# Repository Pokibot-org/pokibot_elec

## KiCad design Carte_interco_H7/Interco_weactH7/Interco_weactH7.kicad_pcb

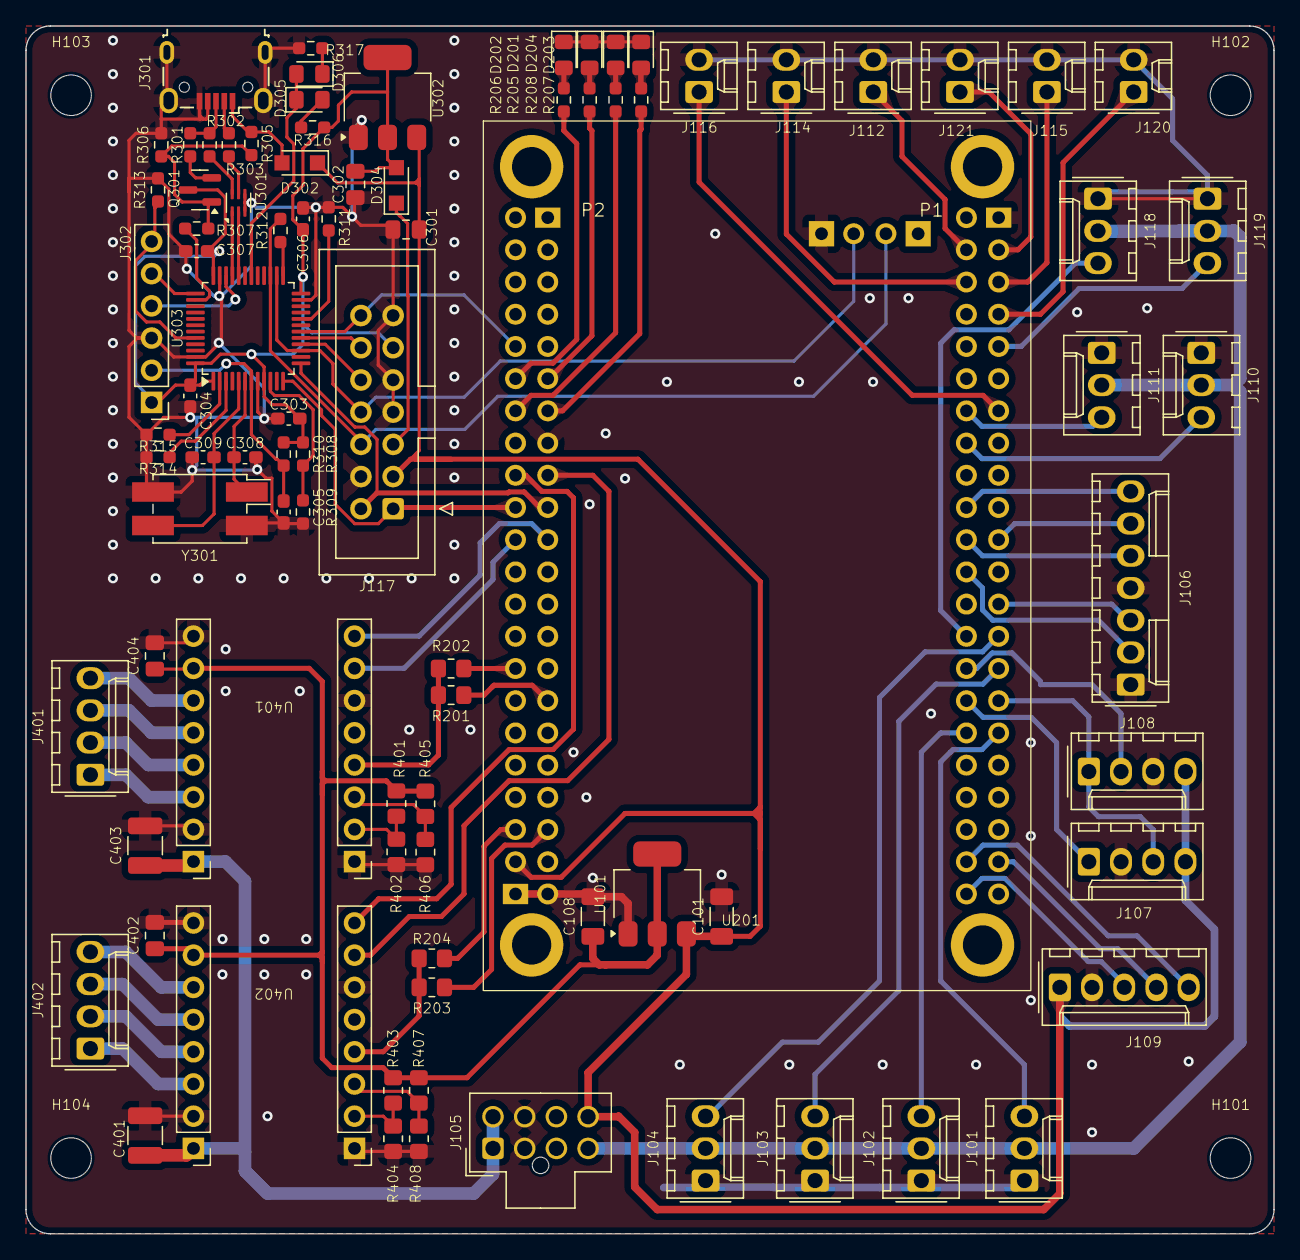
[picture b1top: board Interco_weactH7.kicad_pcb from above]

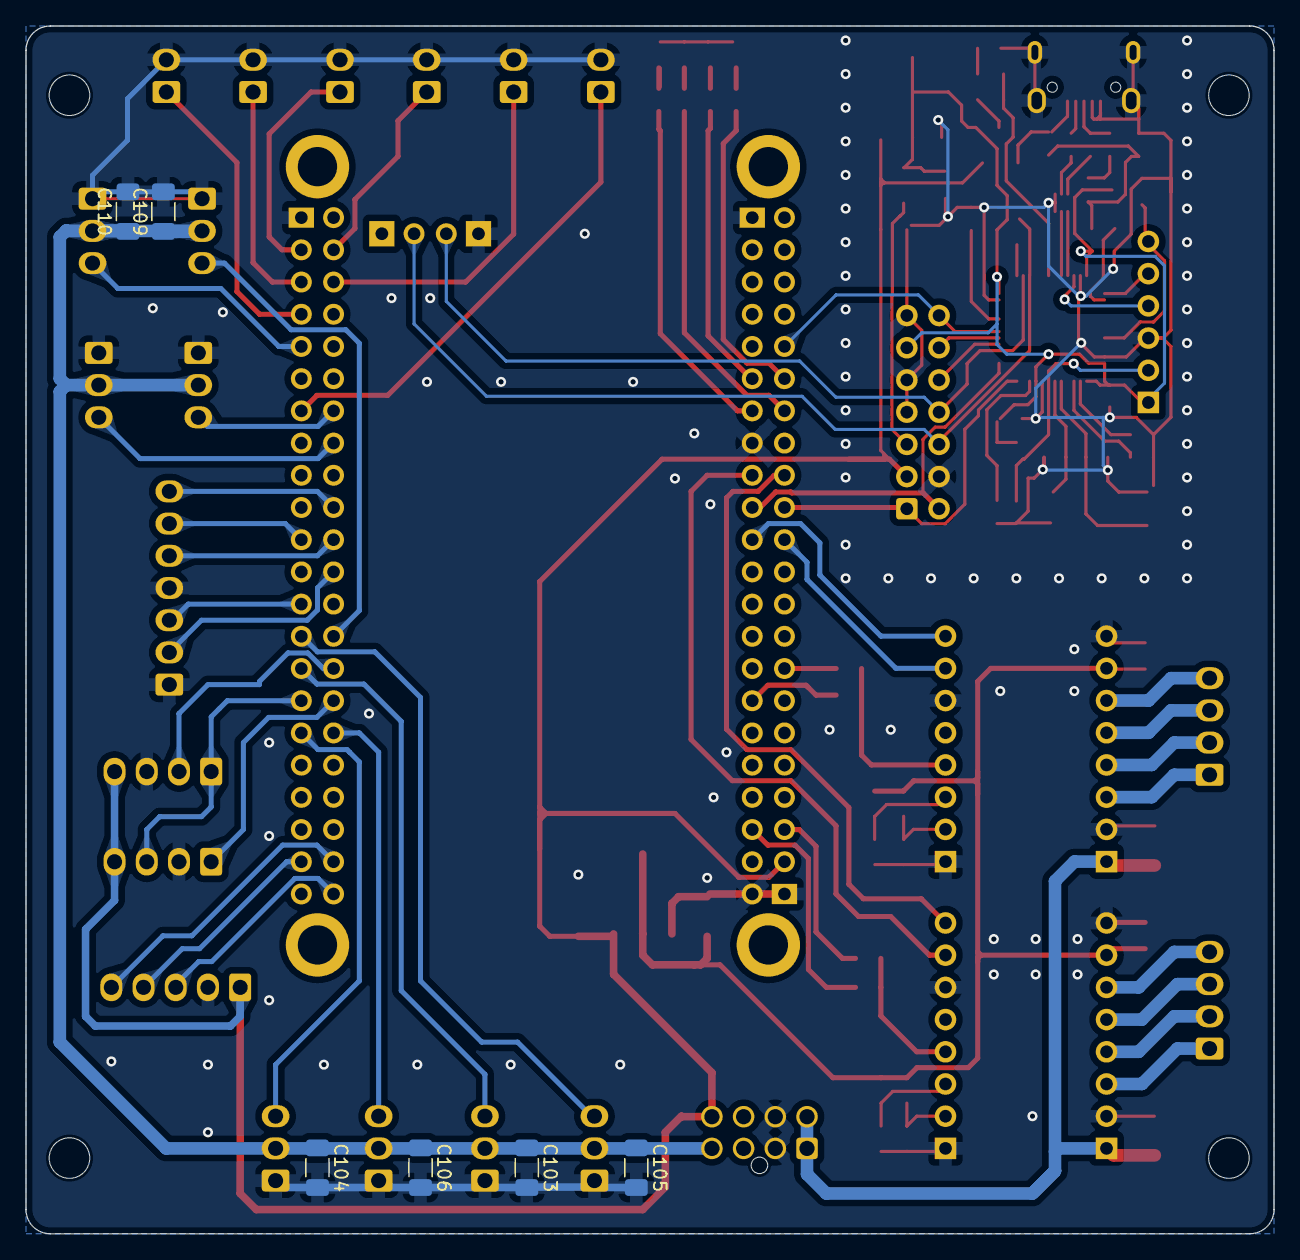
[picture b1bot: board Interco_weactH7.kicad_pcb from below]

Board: 2 copper layers, 98.4 x 95.3 mm, 98 parts (6 on the bottom side), 93 nets.

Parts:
C101, C103, C104, C105, C106, C108, C109, C110: 100n; C_1206_3216Metric_Pad1.33x1.80mm_HandSolder
C301, C302, C402, C404: 10uF; C_0805_2012Metric_Pad1.18x1.45mm_HandSolder
C303, C304, C306, C307: 100nF; C_0603_1608Metric_Pad1.08x0.95mm_HandSolder
C305: C; C_0603_1608Metric_Pad1.08x0.95mm_HandSolder
C308, C309: 20pF; C_0603_1608Metric_Pad1.08x0.95mm_HandSolder
C401, C403: 47uF; C_1210_3225Metric_Pad1.33x2.70mm_HandSolder
D201, D202, D203, D204, D305, D306: LED; LED_0805_2012Metric_Pad1.15x1.40mm_HandSolder
D302, D304: PMEG40T10ER; Nexperia_CFP3_SOD-123W
H101, H102, H103, H104: M1; MountingHole_3.2mm_M3
J101, J110, J118: servo orientation; Molex_KK-254_AE-6410-03A_1x03_P2.54mm_Vertical
J102, J111, J119: servo bras; Molex_KK-254_AE-6410-03A_1x03_P2.54mm_Vertical
J103, J104: servo dicristaline; Molex_KK-254_AE-6410-03A_1x03_P2.54mm_Vertical
J105: POW_access; Molex_Nano-Fit_105310-xx08_2x04_P2.50mm_Vertical
J106: KK-254_AE-6410-07A; Molex_KK-254_AE-6410-07A_1x07_P2.54mm_Vertical
J107, J108: LIDAR; Molex_KK-254_AE-6410-04A_1x04_P2.54mm_Vertical
J109: SNDBOARD; Molex_KK-254_AE-6410-05A_1x05_P2.54mm_Vertical
J112: Tirette; Molex_KK-254_AE-6410-02A_1x02_P2.54mm_Vertical
J114, J116: SWcote; Molex_KK-254_AE-6410-02A_1x02_P2.54mm_Vertical
J115, J121: reset; Molex_KK-254_AE-6410-02A_1x02_P2.54mm_Vertical
J117: Conn_02x07_Odd_Even; IDC-Header_2x07_P2.54mm_Vertical
J120: SWrobot; Molex_KK-254_AE-6410-02A_1x02_P2.54mm_Vertical
J301: 629105150521; USB_Micro-B_Wuerth_629105150521
J302: Conn_01x06_Pin; PinHeader_1x06_P2.54mm_Vertical
J401, J402: KK-254_AE-6410-04A; Molex_KK-254_AE-6410-04A_1x04_P2.54mm_Vertical
Q301: MMBTA44; SOT-23
R201, R202, R203, R204, R401, R402, R403, R404, R405, R406, R407, R408: R_US; R_0805_2012Metric_Pad1.20x1.40mm_HandSolder
R205, R206, R207, R208, R301, R316, R317: 1k; R_0603_1608Metric_Pad0.98x0.95mm_HandSolder
R302, R303: 10R; R_0603_1608Metric_Pad0.98x0.95mm_HandSolder
R305, R315: 10k; R_0603_1608Metric_Pad0.98x0.95mm_HandSolder
R306: 33k; R_0603_1608Metric_Pad0.98x0.95mm_HandSolder
R307, R312: 100R; R_0603_1608Metric_Pad0.98x0.95mm_HandSolder
R308, R309: 4k7; R_0603_1608Metric_Pad0.98x0.95mm_HandSolder
R310, R311, R313: R_US; R_0603_1608Metric_Pad0.98x0.95mm_HandSolder
R314: DNP; R_0603_1608Metric_Pad0.98x0.95mm_HandSolder
U101, U302: LD1117S33TR_SOT223; SOT-223-3_TabPin2
U201: WeAct 32H7xx
U301: ECMF02-2AMX6; ST_UQFN-6L_1.5x1.7mm_P0.5mm
U303: STM32F103CBT6; LQFP-48_7x7mm_P0.5mm
U401, U402: TMC2209
Y301: 8MHz; Crystal_SMD_EuroQuartz_MQ-4Pin_7.0x5.0mm_HandSoldering

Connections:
+3.3VA: C302.1, C303.1, C304.1, C306.1, C307.1, D304.2 (A), J117.11, J302.1, Q301.3 (C), R308.1, R310.1, R316.1, U302.2 (VO), U303.1 (VBAT), U303.9 (VDDA), U303.24 (VDD), U303.36 (VDD), U303.48 (VDD)
+3V3: C108.1, C402.1, C404.1, R401.2, R403.2, R405.2, R407.2, U101.2 (VO), U401.10 (VDD), U402.10 (VDD)
+5V_LOGIC: C101.1, C301.1, D302.1 (K), J105.8, J107.4, J108.4, J109.1, J117.3, U101.3 (VI), U201.P2_42 (5V), U302.3 (VI)
+5V_PWR: C103.1, C104.1, C105.1, C106.1, C109.1, C110.1, J101.2, J102.2, J103.2, J104.2, J105.4, J110.2, J111.2, J118.2, J119.2
+BATT: C401.1, C403.1, J105.1, J105.5, U401.16 (VM), U402.16 (VM)
/LIDAR_RX: J107.1, U201.P1_32 (PC6)
/LIDAR_TX: J107.3, J108.1, U201.P1_31 (PC7)
/MOTOR_MISO: J106.6, U201.P1_21 (PC11)
/MOTOR_MOSI: J106.7, U201.P1_20 (PC12)
/MOTOR_RX(IN): J106.2, U201.P1_24 (PA12)
/MOTOR_SCK: J106.5, U201.P1_22 (PC10)
/MOTOR_TX(OUT): J106.3, U201.P1_25 (PA11)
/PWM_SERVO1: J101.3, U201.P1_33 (PD15)
/PWM_SERVO2: J102.3, U201.P1_34 (PD14)
/PWM_SERVO3: J103.3, U201.P1_29 (PC9)
/PWM_SERVO4: J104.3, U201.P1_27 (PA9)
/PWM_SERVO5: J118.3, U201.P1_28 (PA8)
/PWM_SERVO6: J119.3, U201.P1_9 (PB5)
/SB_RST: J109.3, U201.P1_44 (PB12)
/SB_RX: J109.5, U201.P1_42 (PB14)
/SB_TX: J109.4, U201.P1_41 (PB15)
/TMC/A01: J401.2, U401.13 (A1)
/TMC/A02: J401.1, U401.14 (A2)
/TMC/A11: J402.2, U402.13 (A1)
/TMC/A12: J402.1, U402.14 (A2)
/TMC/B01: J401.3, U401.12 (B1)
/TMC/B02: J401.4, U401.11 (B2)
/TMC/B11: J402.3, U402.12 (B1)
/TMC/B12: J402.4, U402.11 (B2)
/TMC/UART1: R201.2, R202.2, U401.4 (PDN)
/TMC/UART2: R203.2, R204.2, U402.4 (PDN)
/WEACT/DBG1: R205.1, U201.P2_11 (PC0)
/WEACT/DBG2: R206.1, U201.P2_12 (PC1)
/WEACT/DBG3: R207.1, U201.P2_13 (PC2)
/WEACT/DBG4: R208.1, U201.P2_14 (PC3)
/WEACT/PA1: U201.P2_18 (PA1), U402.8 (DIR)
/WEACT/PA4: U201.P2_21 (PA4), U401.8 (DIR)
/WEACT/PB7: J120.1, U201.P1_7 (PB7)
/WEACT/PB8: J114.1, U201.P1_6 (PB8)
/WEACT/PB9: J115.1, U201.P1_5 (PB9)
/WEACT/PD3: J110.3, U201.P1_16 (PD3)
/WEACT/PD5: J111.3, U201.P1_14 (PD5)
/WEACT/PD6: J116.1, U201.P1_13 (PD6)
/WEACT/PE0: J112.1, U201.P1_4 (PE0)
/WEACT/PE1: J121.1, U201.P1_3 (PE1)
/WEACT/TIM2_CH1: U201.P2_22 (PA5), U401.7 (STEP)
/WEACT/TIM3_CH3: J108.2, U201.P1_30 (PC8)
/WEACT/TIM5_CH1: U201.P2_17 (PA0), U402.7 (STEP)
/WEACT/UART7_RX: R202.1, U201.P2_30 (PE7)
/WEACT/UART7_TX: R201.1, U201.P2_31 (PE8)
/WEACT/USART2_RX: J117.1, U201.P2_20 (PA3), U303.12 (PA2)
/WEACT/USART2_TX: J117.2, U201.P2_19 (PA2), U303.13 (PA3)
/WEACT/USART3_RX: R204.1, U201.P2_40 (PB11)
/WEACT/USART3_TX: R203.1, U201.P2_39 (PB10)
/stlink/3V3_TARGET: D304.1 (K), J117.5
/stlink/BOOT0: J302.6, R313.1, U303.44 (BOOT0)
/stlink/LED: D305.1 (K), D306.2 (A), U303.30 (PA9)
/stlink/OSC_IN: C309.1, U303.5 (PD0), Y301.3
/stlink/OSC_OUT: C308.1, U303.6 (PD1), Y301.1
/stlink/SRST: C305.2, J302.2, R310.2, U303.7 (NRST)
/stlink/SWCLK: J302.5, U303.37 (PA14)
/stlink/SWDIO: J302.4, U303.34 (PA13)
/stlink/T_JTCK: J117.8, U201.D3 (SWDCK), U303.15 (PA5), U303.26 (PB13)
/stlink/T_JTDI: J117.12, U303.17 (PA7)
/stlink/T_JTDO: J117.10, U303.16 (PA6)
/stlink/T_JTMS: J117.6, R312.2, U201.D2 (SWDIO), U303.27 (PB14)
/stlink/T_NRST: J117.14, U201.P2_10 (NRST), U303.18 (PB0)
/stlink/USB_RENUM: R307.1, U303.38 (PA15)
GND: C101.2, C103.2, C104.2, C105.2, C106.2, C108.2, C109.2, C110.2, C301.2, C302.2, C303.2, C304.2, C305.1, C306.2, C307.2, C308.2, C309.2, C401.2, C402.2, C403.2, C404.2, D201.1 (K), D202.1 (K), D203.1 (K), D204.1 (K), J101.1, J102.1, J103.1, J104.1, J105.2, J105.6, J106.1, J106.4, J107.2, J108.3, J109.2, J110.1, J111.1, J112.2, J114.2, J115.2, J116.2, J117.4, J117.7, J117.9, J117.13, J118.1, J119.1, J120.2, J121.2, J301.4 (ID), J301.5 (GND), J301.6 (Shield), J302.3, R306.2, R309.2, R311.2, R313.2, R314.2, R315.2, R317.2, R402.1, R404.1, R406.1, R408.1, U101.1 (GND), U201.D4 (GND), U201.P1_1 (GND), U201.P2_1 (GND), U201.P2_15 (GND), U201.P2_43 (GND), U201.P2_44 (GND), U301.3 (GND), U301.4 (NC), U302.1 (GND), U303.8 (VSSA), U303.23 (VSS), U303.35 (VSS), U303.47 (VSS), U401.1 (EN), U401.6 (CLK), U401.9 (GND), U401.15 (GND), U402.1 (EN), U402.6 (CLK), U402.9 (GND), U402.15 (GND), Y301.2, Y301.4
unnamed: D201.2 (A), R205.2
unnamed: D202.2 (A), R206.2
unnamed: D203.2 (A), R207.2
unnamed: D204.2 (A), R208.2
unnamed: D302.2 (A), J301.1 (VBUS), R305.1
unnamed: D305.2 (A), R316.2
unnamed: D306.1 (K), R317.1
unnamed: J301.3 (D+), R301.2, R302.1
unnamed: J301.2 (D-), R303.1
unnamed: Q301.1 (B), R305.2, R306.1, R307.2
unnamed: Q301.2 (E), R301.1
unnamed: U301.1 (D+_in), U303.33 (PA12)
unnamed: R302.2, U301.6 (D+_out)
unnamed: U301.2 (D-_in), U303.32 (PA11)
unnamed: R303.2, U301.5 (D-_out)
unnamed: R308.2, R309.1, U303.10 (PA0)
unnamed: R311.1, U303.20 (PB2)
unnamed: R312.1, U303.25 (PB12)
unnamed: R315.1, U303.2 (PC13)
unnamed: R314.1, U303.3 (PC14)
unnamed: R401.1, R402.2, U401.2 (MS1)
unnamed: R405.1, R406.2, U401.3 (MS2)
unnamed: R403.1, R404.2, U402.2 (MS1)
unnamed: R407.1, R408.2, U402.3 (MS2)

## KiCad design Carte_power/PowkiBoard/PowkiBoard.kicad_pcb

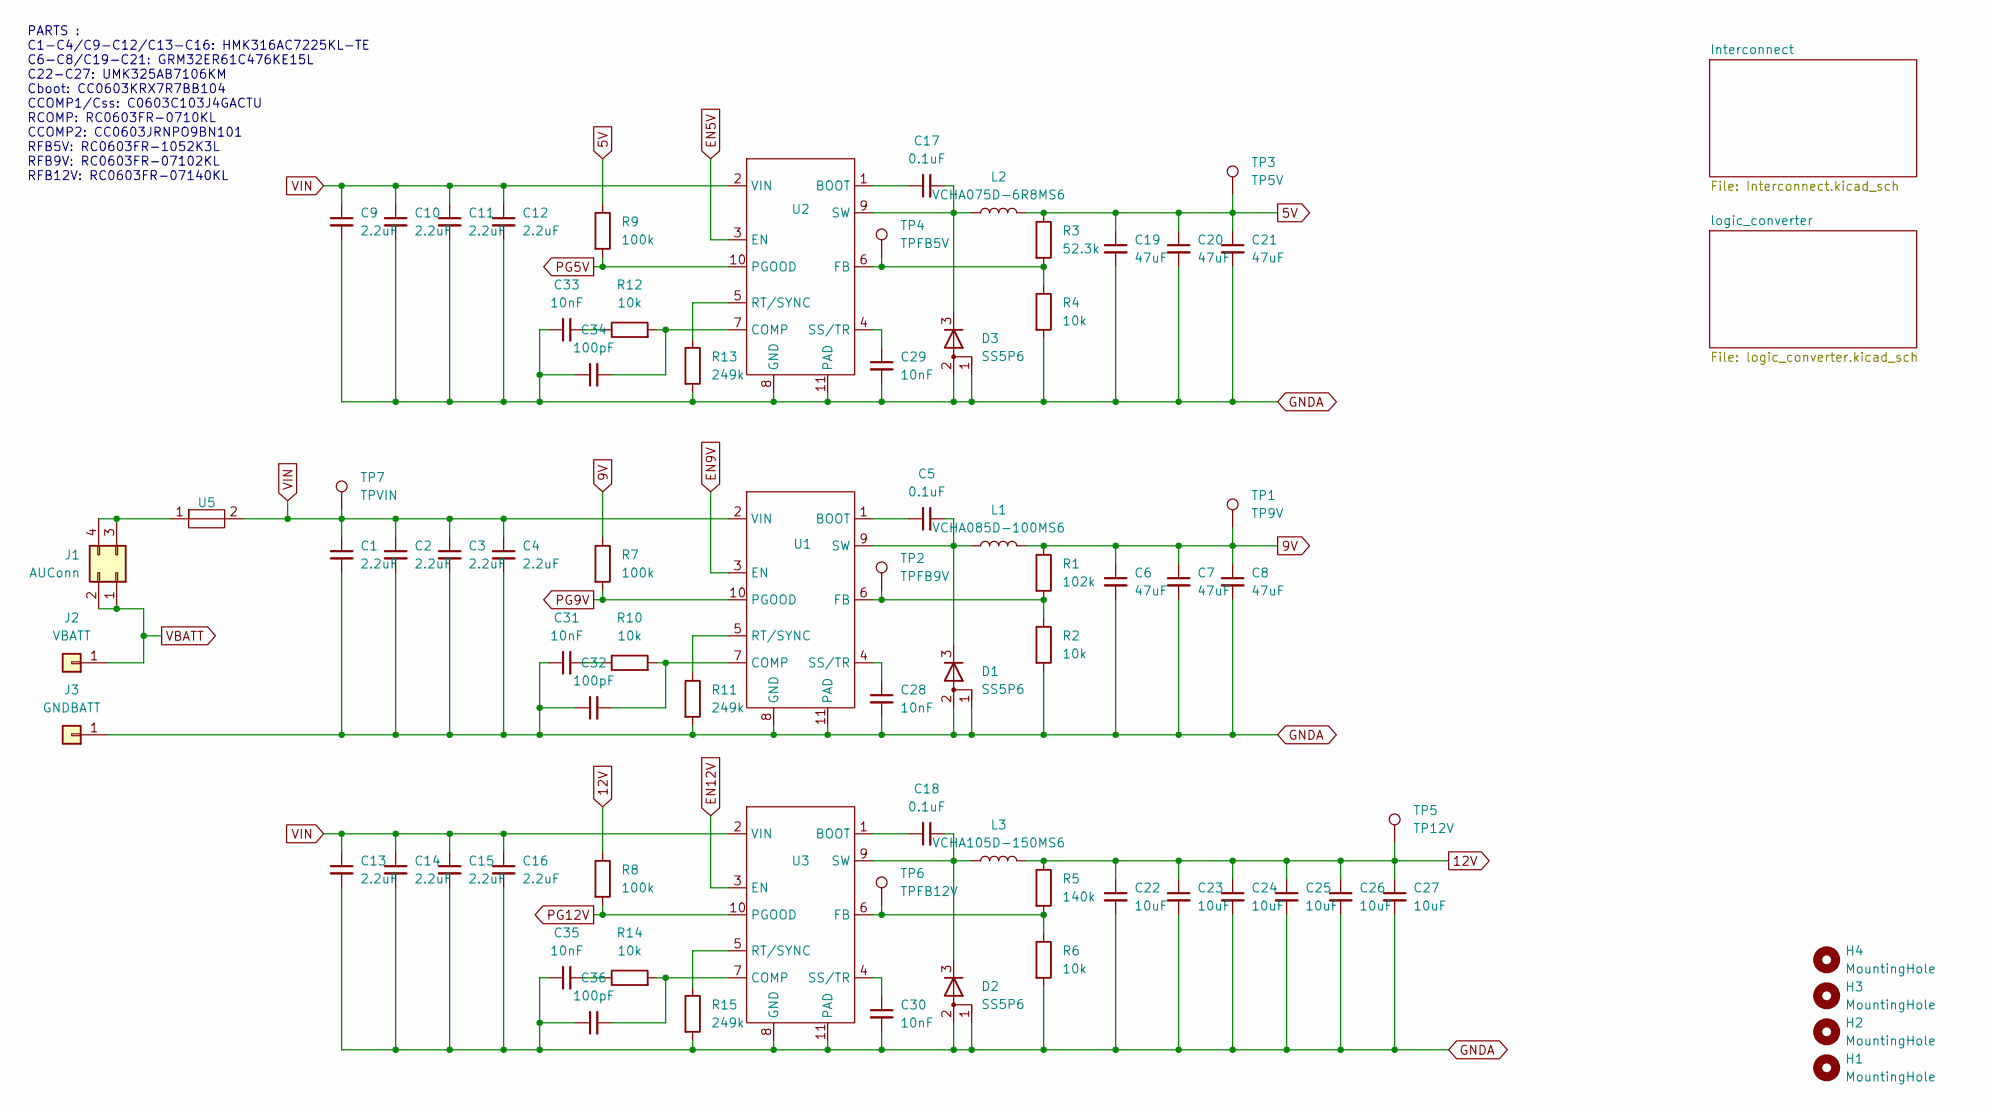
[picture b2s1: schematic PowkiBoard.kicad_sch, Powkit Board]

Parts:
C1, C2, C3, C4, C9, C10, C11, C12, C13, C14, C15, C16: 2.2uF; C_1206_3216Metric
C5, C17, C18: 0.1uF; C_0603_1608Metric
C6, C7, C8, C19, C20, C21: 47uF; C_1210_3225Metric
C22, C23, C24, C25, C26, C27: 10uF; C_1210_3225Metric
C28, C29, C30, C31, C33, C35: 10nF; C_0603_1608Metric
C32, C34, C36: 100pF; C_0603_1608Metric
D1, D2, D3: SS5P6; TO-277A
H1, H2, H3, H4: MountingHole; MountingHole_3.2mm_M3
J1: AUConn; Molex_Nano-Fit_105310-xx04_2x02_P2.50mm_Vertical
J2: VBATT; BATT_CONN
J3: GNDBATT; BATT_CONN
L1: VCHA085D-100MS6
L2: VCHA075D-6R8MS6
L3: VCHA105D-150MS6
R1: 102k; R_0603_1608Metric
R2, R4, R6, R10, R12, R14: 10k; R_0603_1608Metric
R3: 52.3k; R_0603_1608Metric
R5: 140k; R_0603_1608Metric
R7, R8, R9: 100k; R_0603_1608Metric
R11, R13, R15: 249k; R_0603_1608Metric
TP1: TP9V; TestPoint_Pad_D1.5mm
TP2: TPFB9V; TestPoint_Pad_D1.5mm
TP3: TP5V; TestPoint_Pad_D1.5mm
TP4: TPFB5V; TestPoint_Pad_D1.5mm
TP5: TP12V; TestPoint_Pad_D1.5mm
TP6: TPFB12V; TestPoint_Pad_D1.5mm
TP7: TPVIN; TestPoint_Pad_D1.5mm
U1, U2, U3: WDFN-10-1EP_3x3mm_P0.5mm_EP1.8x2.5mm
U5: 20x5_fuseholder

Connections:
5V: C19.1, C20.1, C21.1, L2.2, R3.1, R9.1, TP3.1; also elsewhere on the board
9V: C6.1, C7.1, C8.1, L1.2, R1.1, R7.1, TP1.1; also elsewhere on the board
12V: C22.1, C23.1, C24.1, C25.1, C26.1, C27.1, L3.2, R5.1, R8.1, TP5.1; also elsewhere on the board
EN12V: U1.3 (EN), U2.3 (EN), U3.3 (EN); also elsewhere on the board
GNDA: C1.2, C2.2, C3.2, C4.2, C6.2, C7.2, C8.2, C9.2, C10.2, C11.2, C12.2, C13.2, C14.2, C15.2, C16.2, C19.2, C20.2, C21.2, C22.2, C23.2, C24.2, C25.2, C26.2, C27.2, C28.2, C29.2, C30.2, C31.1, C32.1, C33.1, C34.1, C35.1, C36.1, D1.1 (A), D1.2 (A), D2.1 (A), D2.2 (A), D3.1 (A), D3.2 (A), J3.1, R2.2, R4.2, R6.2, R11.2, R13.2, R15.2, U1.8 (GND), U1.11 (PAD), U2.8 (GND), U2.11 (PAD), U3.8 (GND), U3.11 (PAD); also elsewhere on the board
unnamed: C31.2, R10.1
unnamed: C33.2, R12.1
unnamed: C35.2, R14.1
unnamed: C5.2, D1.3 (K), L1.1, U1.9 (SW)
unnamed: C18.2, D2.3 (K), L3.1, U3.9 (SW)
unnamed: C17.2, D3.3 (K), L2.1, U2.9 (SW)
unnamed: J1.3, J1.4, U5.1
unnamed: C5.1, U1.1 (BOOT)
unnamed: C32.2, R10.2, U1.7 (COMP)
unnamed: R1.2, R2.1, TP2.1, U1.6 (FB)
unnamed: R11.1, U1.5 (RT/SYNC)
unnamed: C28.1, U1.4 (SS/TR)
unnamed: C17.1, U2.1 (BOOT)
unnamed: C34.2, R12.2, U2.7 (COMP)
unnamed: R3.2, R4.1, TP4.1, U2.6 (FB)
unnamed: R13.1, U2.5 (RT/SYNC)
unnamed: C29.1, U2.4 (SS/TR)
unnamed: C18.1, U3.1 (BOOT)
unnamed: C36.2, R14.2, U3.7 (COMP)
unnamed: R5.2, R6.1, TP6.1, U3.6 (FB)
unnamed: R15.1, U3.5 (RT/SYNC)
unnamed: C30.1, U3.4 (SS/TR)
PG5V: R9.2, U2.10 (PGOOD); also elsewhere on the board
PG9V: R7.2, U1.10 (PGOOD); also elsewhere on the board
PG12V: R8.2, U3.10 (PGOOD); also elsewhere on the board
VBATT: J1.1, J1.2, J2.1; also elsewhere on the board
VIN: C1.1, C2.1, C3.1, C4.1, C9.1, C10.1, C11.1, C12.1, C13.1, C14.1, C15.1, C16.1, TP7.1, U1.2 (VIN), U2.2 (VIN), U3.2 (VIN), U5.2; also elsewhere on the board

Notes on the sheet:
PARTS : C1-C4/C9-C12/C13-C16: HMK316AC7225KL-TE C6-C8/C19-C21: GRM32ER61C476KE15L C22-C27: UMK325AB7106KM Cboot: CC0603KRX7R7BB104 CCOMP1/Css: C0603C103J4GACTU RCOMP: RC0603FR-0710KL CCOMP2: CC0603JRNPO9BN101 RFB5V: RC0603FR-1052K3L RFB9V: RC0603FR-07102KL RFB12V: RC0603FR-07140KL

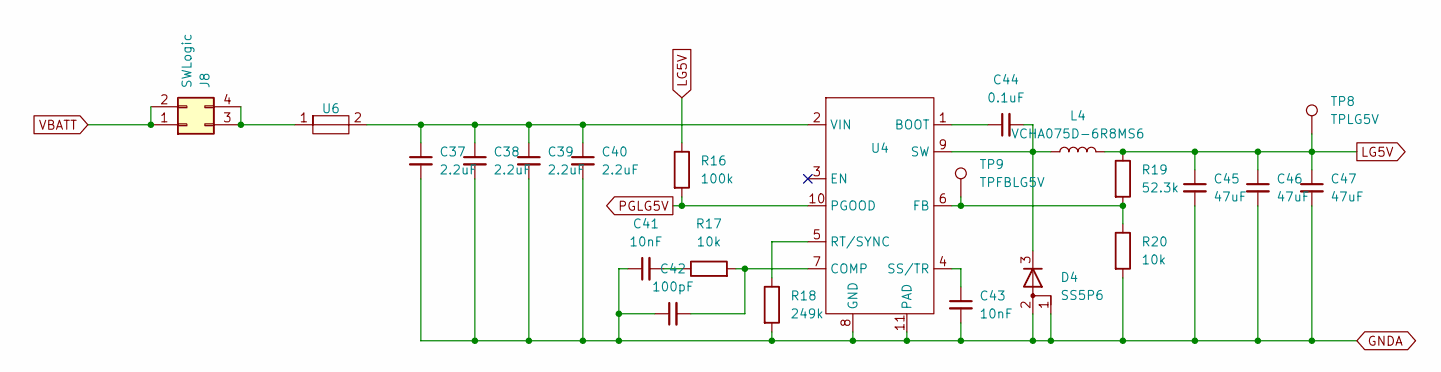
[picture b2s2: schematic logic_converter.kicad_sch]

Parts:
C37, C38, C39, C40: 2.2uF; C_1206_3216Metric
C41, C43: 10nF; C_0603_1608Metric
C42: 100pF; C_0603_1608Metric
C44: 0.1uF; C_0603_1608Metric
C45, C46, C47: 47uF; C_1210_3225Metric
D4: SS5P6; TO-277A
J8: SWLogic; Molex_Nano-Fit_105310-xx04_2x02_P2.50mm_Vertical
L4: VCHA075D-6R8MS6
R16: 100k; R_0603_1608Metric
R17, R20: 10k; R_0603_1608Metric
R18: 249k; R_0603_1608Metric
R19: 52.3k; R_0603_1608Metric
TP8: TPLG5V; TestPoint_Pad_D1.5mm
TP9: TPFBLG5V; TestPoint_Pad_D1.5mm
U4: WDFN-10-1EP_3x3mm_P0.5mm_EP1.8x2.5mm
U6: 20x5_fuseholder

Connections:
GNDA: C37.2, C38.2, C39.2, C40.2, C41.1, C42.1, C43.2, C45.2, C46.2, C47.2, D4.1 (A), D4.2 (A), R18.2, R20.2, U4.8 (GND), U4.11 (PAD); also elsewhere on the board
LG5V: C45.1, C46.1, C47.1, L4.2, R16.1, R19.1, TP8.1; also elsewhere on the board
unnamed: C41.2, R17.1
unnamed: C44.2, D4.3 (K), L4.1, U4.9 (SW)
unnamed: J8.3, J8.4, U6.1
unnamed: C44.1, U4.1 (BOOT)
unnamed: C42.2, R17.2, U4.7 (COMP)
unnamed: R19.2, R20.1, TP9.1, U4.6 (FB)
unnamed: R18.1, U4.5 (RT/SYNC)
unnamed: C43.1, U4.4 (SS/TR)
unnamed: C37.1, C38.1, C39.1, C40.1, U4.2 (VIN), U6.2
PGLG5V: R16.2, U4.10 (PGOOD); also elsewhere on the board
VBATT: J8.1, J8.2; also elsewhere on the board

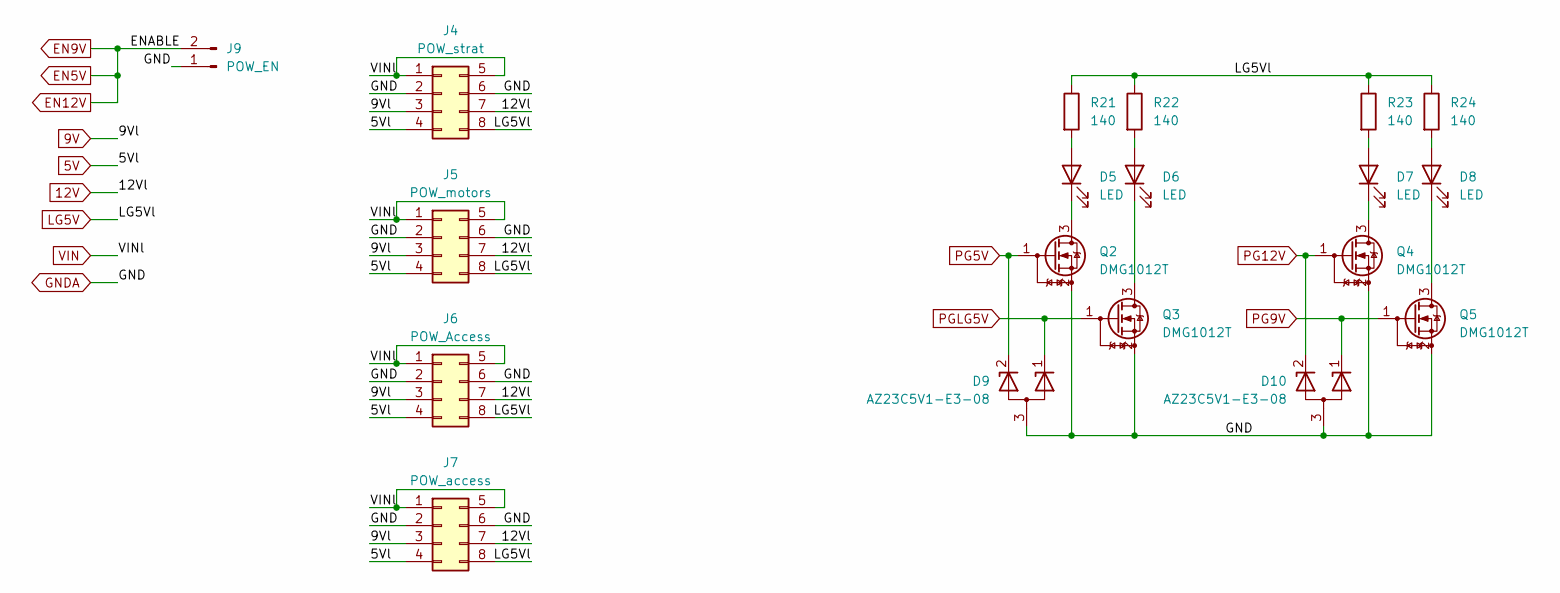
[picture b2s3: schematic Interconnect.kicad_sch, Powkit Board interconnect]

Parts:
D5, D6, D7, D8: LED; LED_D3.0mm
D9, D10: AZ23C5V1-E3-08; SOT-23
J4: POW_strat; Molex_Nano-Fit_105314-xx08_2x04_P2.50mm_Horizontal
J5: POW_motors; Molex_Nano-Fit_105314-xx08_2x04_P2.50mm_Horizontal
J6: POW_Access; Molex_Nano-Fit_105314-xx08_2x04_P2.50mm_Horizontal
J7: POW_access; Molex_Nano-Fit_105314-xx08_2x04_P2.50mm_Horizontal
J9: POW_EN; Molex_KK-254_AE-6410-02A_1x02_P2.54mm_Vertical
Q2, Q3, Q4, Q5: DMG1012T; SOT-523
R21, R22, R23, R24: 140; R_0603_1608Metric

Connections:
5V: J4.4, J5.4, J6.4, J7.4; also elsewhere on the board
9V: J4.3, J5.3, J6.3, J7.3; also elsewhere on the board
12V: J4.7, J5.7, J6.7, J7.7; also elsewhere on the board
EN12V: J9.2; also elsewhere on the board
GNDA: D9.3 (A), D10.3 (A), J4.2, J4.6, J5.2, J5.6, J6.2, J6.6, J7.2, J7.6, J9.1, Q2.2 (S), Q3.2 (S), Q4.2 (S), Q5.2 (S); also elsewhere on the board
LG5V: J4.8, J5.8, J6.8, J7.8, R21.1, R22.1, R23.1, R24.1; also elsewhere on the board
unnamed: D5.2 (A), R21.2
unnamed: D5.1 (K), Q2.3 (D)
unnamed: D6.2 (A), R22.2
unnamed: D6.1 (K), Q3.3 (D)
unnamed: D7.2 (A), R23.2
unnamed: D7.1 (K), Q4.3 (D)
unnamed: D8.2 (A), R24.2
unnamed: D8.1 (K), Q5.3 (D)
PG5V: D9.2 (K), Q2.1 (G); also elsewhere on the board
PG9V: D10.1 (K), Q5.1 (G); also elsewhere on the board
PG12V: D10.2 (K), Q4.1 (G); also elsewhere on the board
PGLG5V: D9.1 (K), Q3.1 (G); also elsewhere on the board
VIN: J4.1, J4.5, J5.1, J5.5, J6.1, J6.5, J7.1, J7.5; also elsewhere on the board

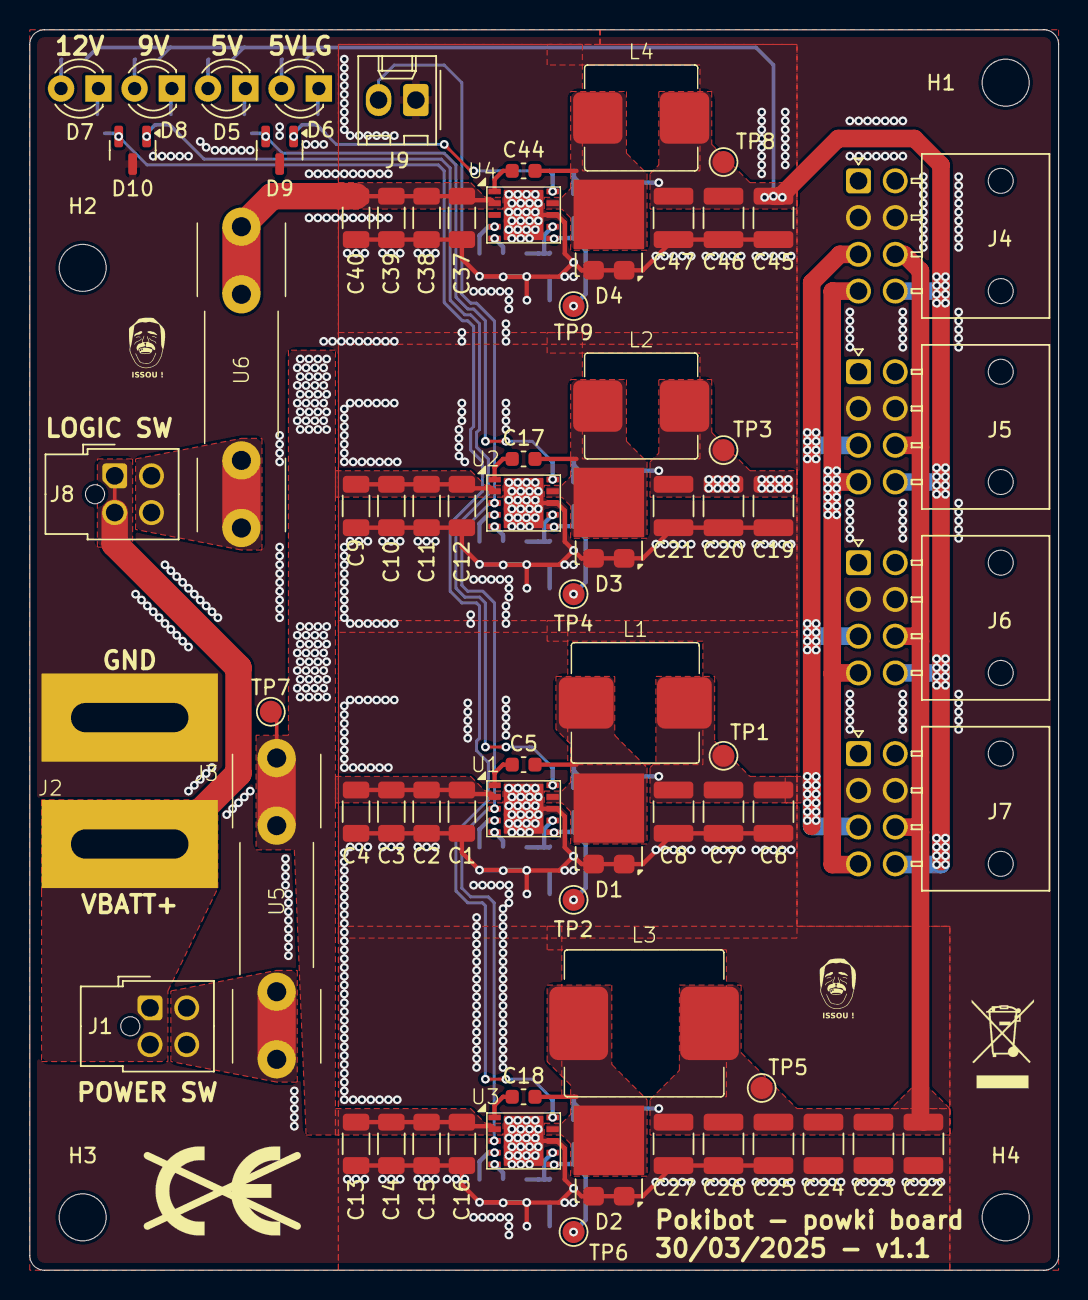
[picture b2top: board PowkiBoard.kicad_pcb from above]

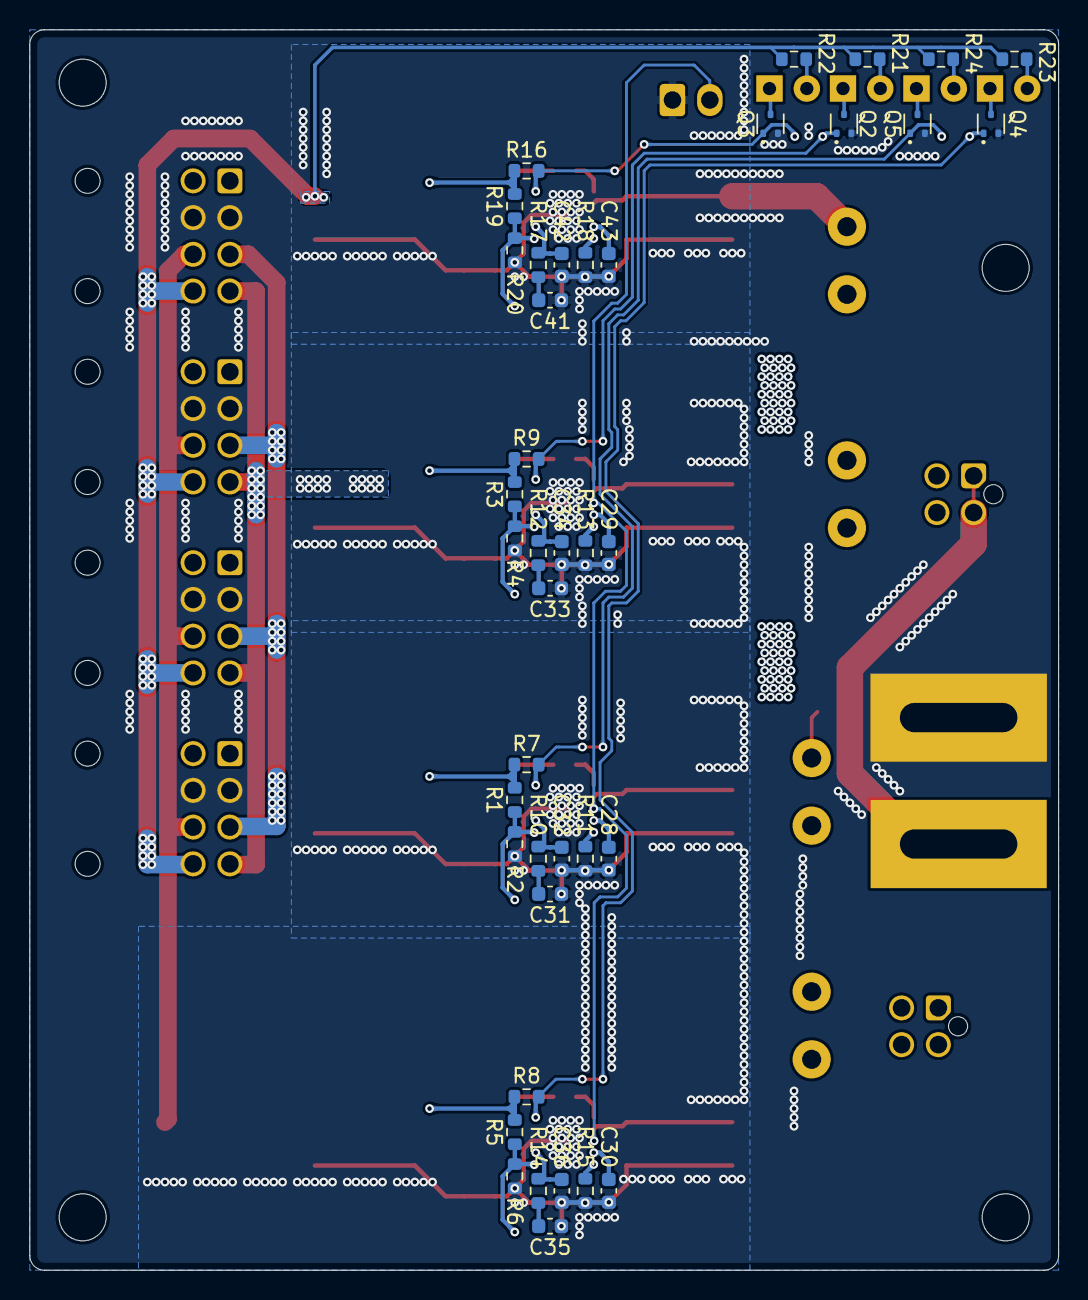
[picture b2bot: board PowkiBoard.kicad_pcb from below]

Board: 4 copper layers, 70.0 x 84.4 mm, 119 parts (40 on the bottom side), 51 nets.

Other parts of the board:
logo1: CE-Logo_8.5x6mm_SilkScreen
logo2: WEEE-Logo_4.2x6mm_SilkScreen

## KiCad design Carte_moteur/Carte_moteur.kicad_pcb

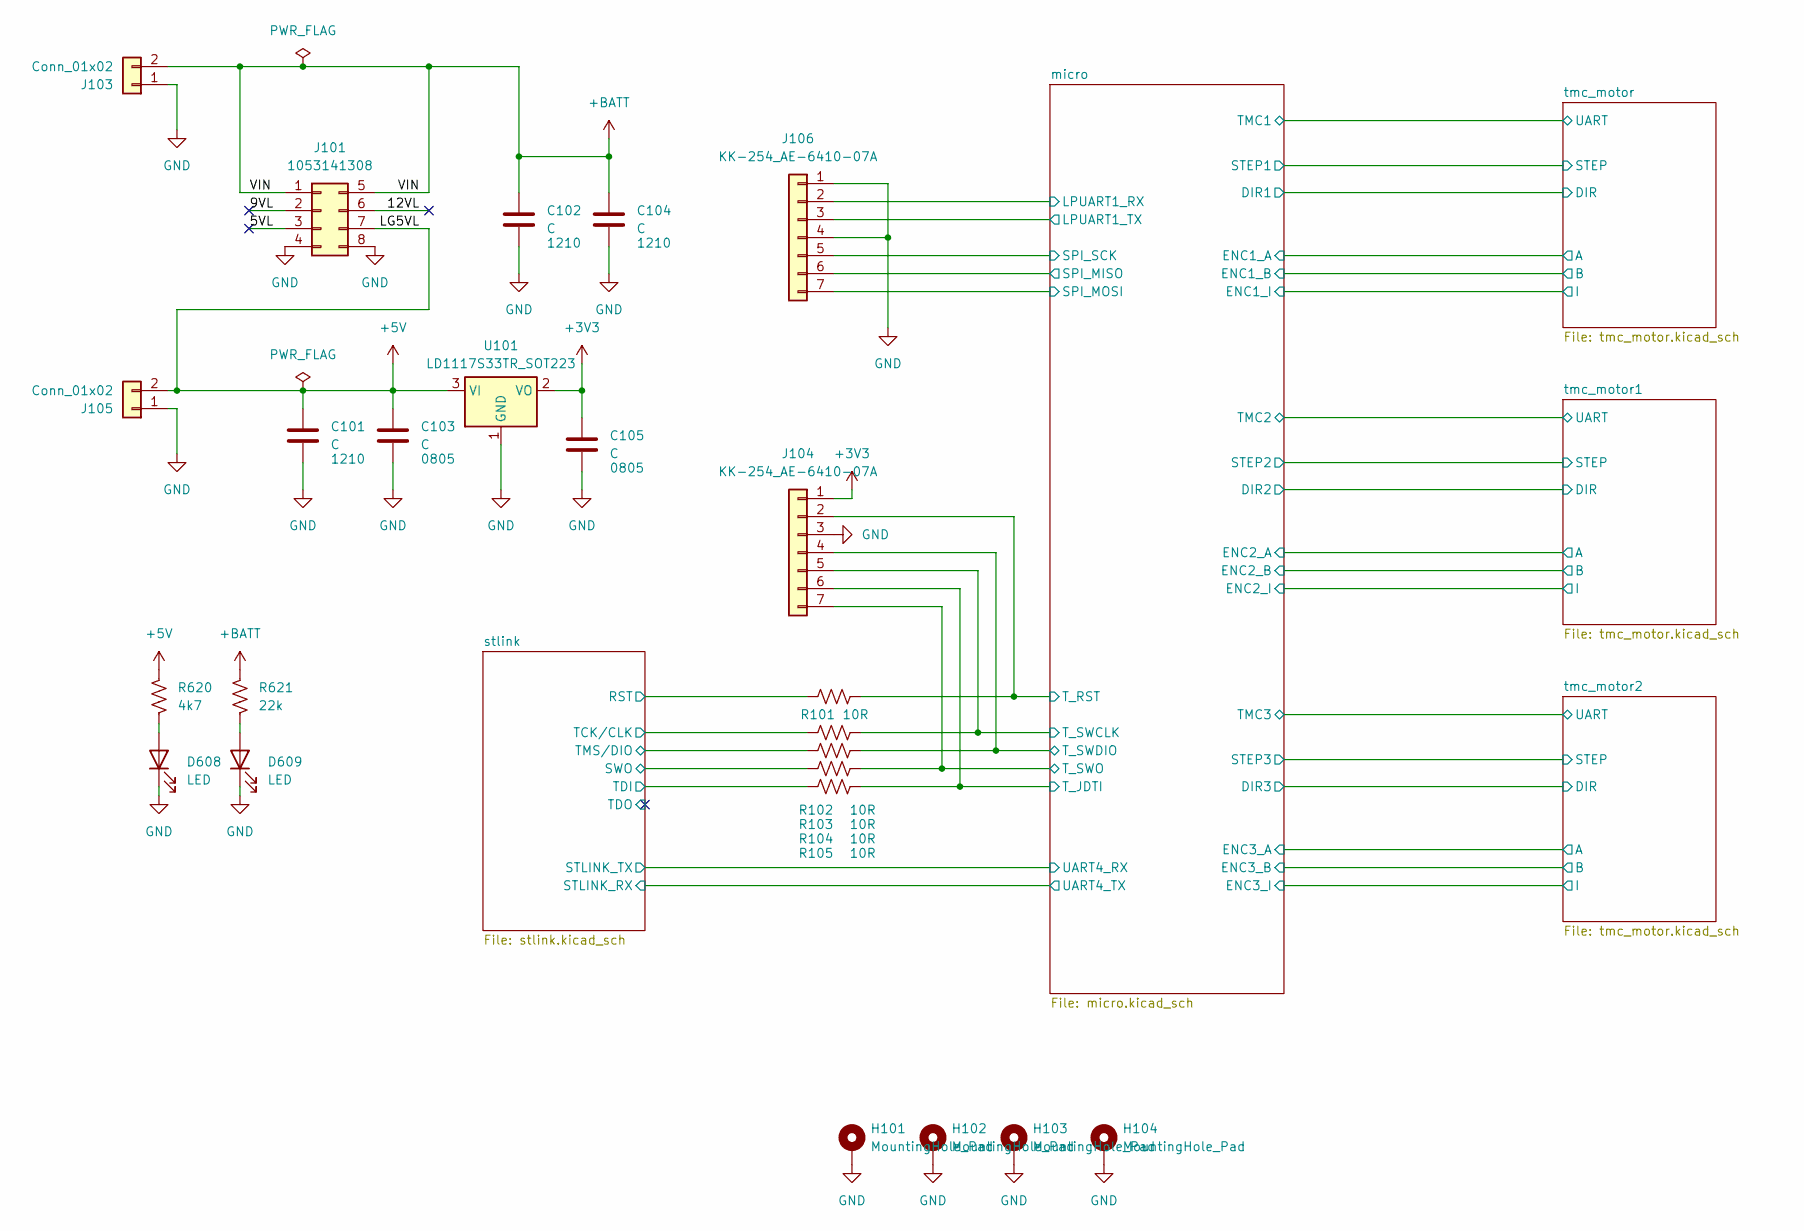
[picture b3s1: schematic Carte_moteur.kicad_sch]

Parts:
C101, C102, C104: C; C_1210_3225Metric_Pad1.33x2.70mm_HandSolder
C103, C105: C; C_0805_2012Metric_Pad1.18x1.45mm_HandSolder
D608, D609: LED; LED_0805_2012Metric_Pad1.15x1.40mm_HandSolder
H101, H102, H103, H104: MountingHole_Pad; MountingHole_3.2mm_M3_DIN965_Pad
J101: 1053141308; Molex_Nano-Fit_105310-xx08_2x04_P2.50mm_Vertical
J103, J105: Conn_01x02; Molex_KK-396_A-41791-0002_1x02_P3.96mm_Vertical
J104, J106: KK-254_AE-6410-07A; Molex_KK-254_AE-6410-07A_1x07_P2.54mm_Vertical
R101, R102, R103, R104, R105: 10R; R_0603_1608Metric_Pad0.98x0.95mm_HandSolder
R620: 4k7; R_0603_1608Metric_Pad0.98x0.95mm_HandSolder
R621: 22k; R_0603_1608Metric_Pad0.98x0.95mm_HandSolder
U101: LD1117S33TR_SOT223; SOT-223-3_TabPin2

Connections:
+3V3: C105.1, J104.1, U101.2 (VO); also elsewhere on the board
+5V: C101.1, C103.1, J101.7, J105.2, R620.1, U101.3 (VI); also elsewhere on the board
+BATT: C102.1, C104.1, J101.1, J101.5, J103.2, R621.1; also elsewhere on the board
/5VL: J101.3
/9VL: J101.2
/12VL: J101.6
/micro/LPUART1_RX: J106.2; also elsewhere on the board
/micro/LPUART1_TX: J106.3; also elsewhere on the board
/micro/SPI1_MISO: J106.6; also elsewhere on the board
/micro/SPI1_MOSI: J106.7; also elsewhere on the board
/micro/SPI1_SCK: J106.5; also elsewhere on the board
/micro/T_JDTI: J104.6, R105.1; also elsewhere on the board
/micro/T_RST: J104.2, R101.1; also elsewhere on the board
/micro/T_SWCLK: J104.5, R102.1; also elsewhere on the board
/micro/T_SWDIO: J104.4, R103.1; also elsewhere on the board
/micro/T_SWO: J104.7, R104.1; also elsewhere on the board
/stlink/T_JTCK: R102.2; also elsewhere on the board
/stlink/T_JTDI: R105.2; also elsewhere on the board
/stlink/T_JTMS: R103.2; also elsewhere on the board
/stlink/T_NRST: R101.2; also elsewhere on the board
/stlink/T_SWO: R104.2; also elsewhere on the board
GND: C101.2, C102.2, C103.2, C104.2, C105.2, D608.1 (K), D609.1 (K), H101.1, H102.1, H103.1, H104.1, J101.4, J101.8, J103.1, J104.3, J105.1, J106.1, J106.4, U101.1 (GND); also elsewhere on the board
unnamed: D608.2 (A), R620.2
unnamed: D609.2 (A), R621.2
